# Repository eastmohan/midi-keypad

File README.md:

# midi-keypad
A compact, custom-designed USB MIDI controller built around the Waveshare ESP32-S3-ZERO. It has 7 key inputs, a daisy-chained chain of addressable RGB LEDs for visual feedback, and a rotary encoder with a push-button for volume control.

Components
Microcontroller (U1): Waveshare ESP32-S3-ZERO (providing native USB support for direct MIDI communication).
EC11 Rotary Encoder
8*SK6812 Mini-e LEDs
PCB

Key Inputs (J1): Set as a pin header in the schematic, but actually connects to a custom footprint of exposed pads (conductive keys):

Rotary Encoder (SW1): Incremental rotary encoder with an integrated push switch (rcswitch) for navigation or volume adjustment.

Addressable LEDs (D1–D8): 8x SK6812MINI-E RGB LEDs wired in a serial data chain.

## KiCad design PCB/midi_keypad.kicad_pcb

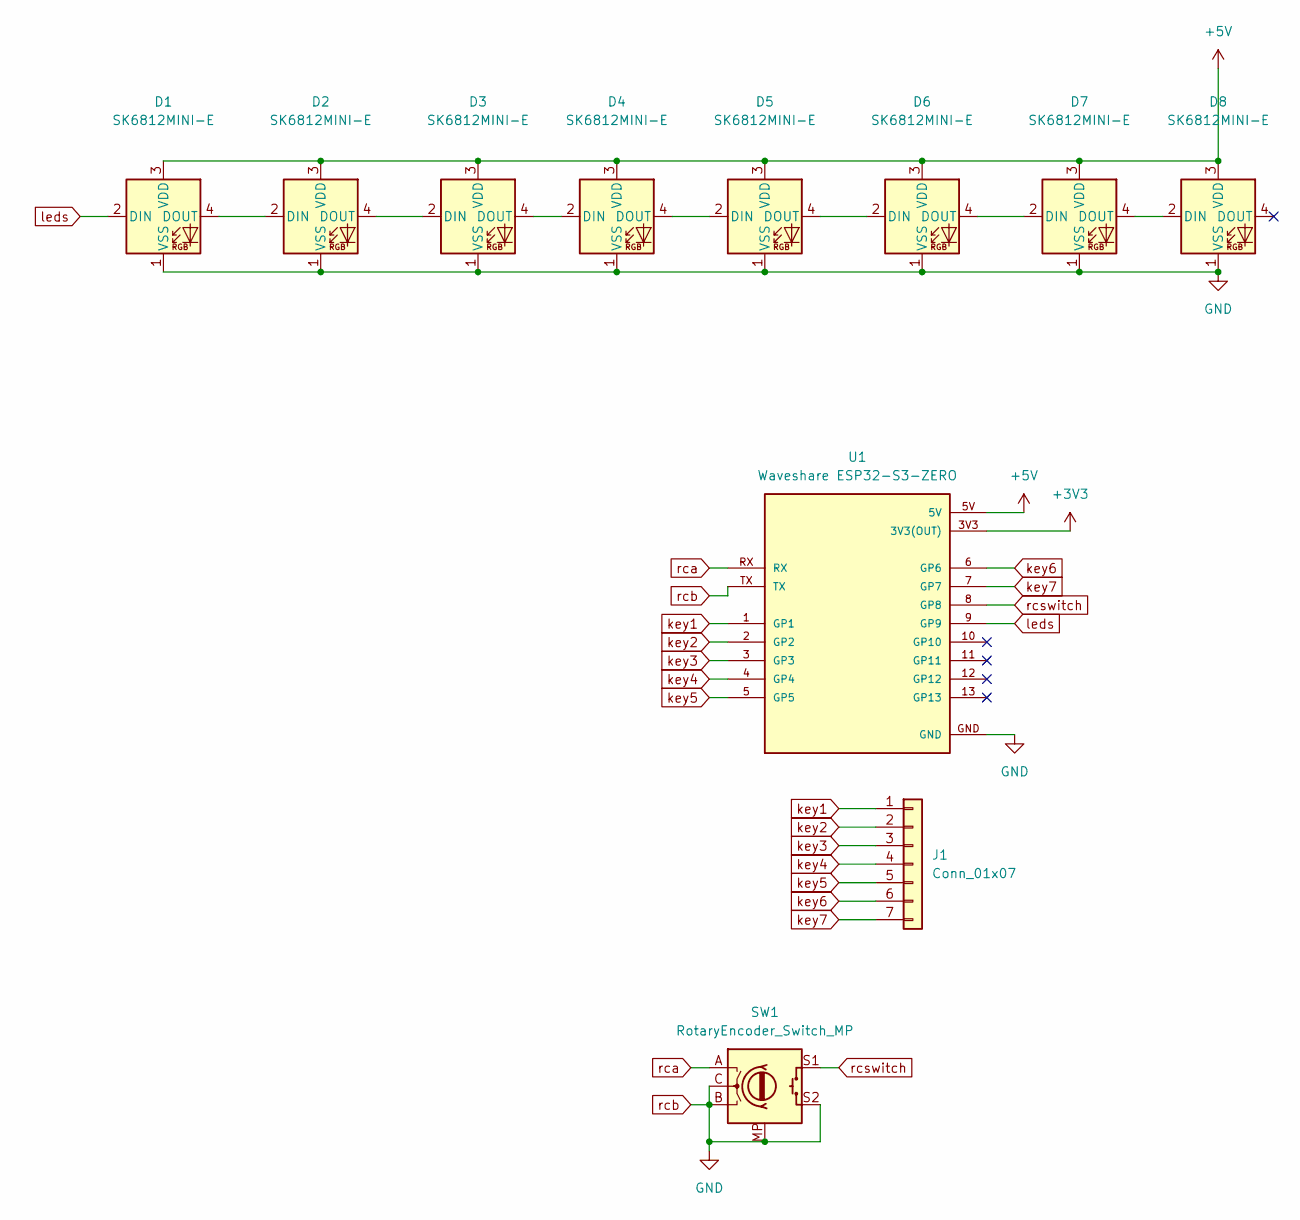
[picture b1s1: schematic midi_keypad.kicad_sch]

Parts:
D1, D2, D3, D4, D5, D6, D7, D8: SK6812MINI-E; LED_SK6812MINI-E_3.2x2.8mm_P1.5mm_ReverseMount
J1: Conn_01x07; capacitive keys
SW1: RotaryEncoder_Switch_MP; RotaryEncoder_Alps_EC11E-Switch_Vertical_H20mm
U1: Waveshare ESP32-S3-ZERO; Waveshare ESP32-S3-Zero; PARTREV NA

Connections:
+3V3: U1.3V3 (3V3(OUT))
+5V: D1.3 (VDD), D2.3 (VDD), D3.3 (VDD), D4.3 (VDD), D5.3 (VDD), D6.3 (VDD), D7.3 (VDD), D8.3 (VDD), U1.5V
unnamed: D1.4 (DOUT), D2.2 (DIN)
unnamed: D2.4 (DOUT), D3.2 (DIN)
unnamed: D3.4 (DOUT), D4.2 (DIN)
unnamed: D4.4 (DOUT), D5.2 (DIN)
unnamed: D5.4 (DOUT), D6.2 (DIN)
unnamed: D6.4 (DOUT), D7.2 (DIN)
unnamed: D7.4 (DOUT), D8.2 (DIN)
key1: J1.1, U1.1 (GP1)
key2: J1.2, U1.2 (GP2)
key3: J1.3, U1.3 (GP3)
key4: J1.4, U1.4 (GP4)
key5: J1.5, U1.5 (GP5)
key6: J1.6, U1.6 (GP6)
key7: J1.7, U1.7 (GP7)
leds: D1.2 (DIN), U1.9 (GP9)
rca: SW1.A, U1.RX
rcb: D1.1 (VSS), D2.1 (VSS), D3.1 (VSS), D4.1 (VSS), D5.1 (VSS), D6.1 (VSS), D7.1 (VSS), D8.1 (VSS), SW1.B, SW1.C, SW1.MP, SW1.S2, U1.GND, U1.TX
rcswitch: SW1.S1, U1.8 (GP8)

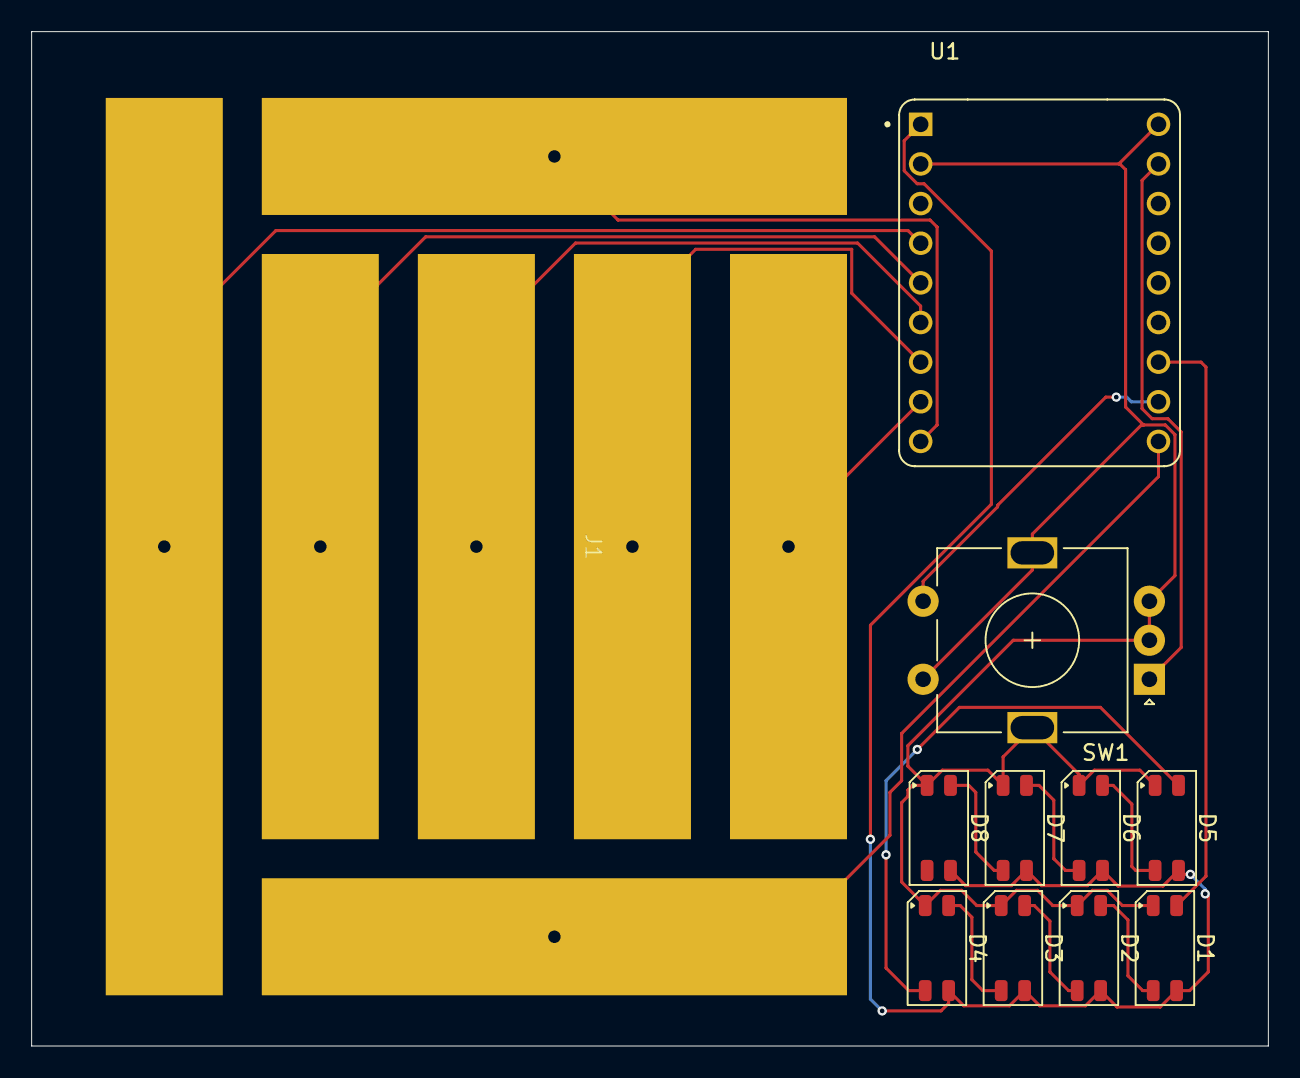
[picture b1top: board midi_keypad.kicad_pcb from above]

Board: 2 copper layers, 79.2 x 65.0 mm, 11 parts (0 on the bottom side), 19 nets.
